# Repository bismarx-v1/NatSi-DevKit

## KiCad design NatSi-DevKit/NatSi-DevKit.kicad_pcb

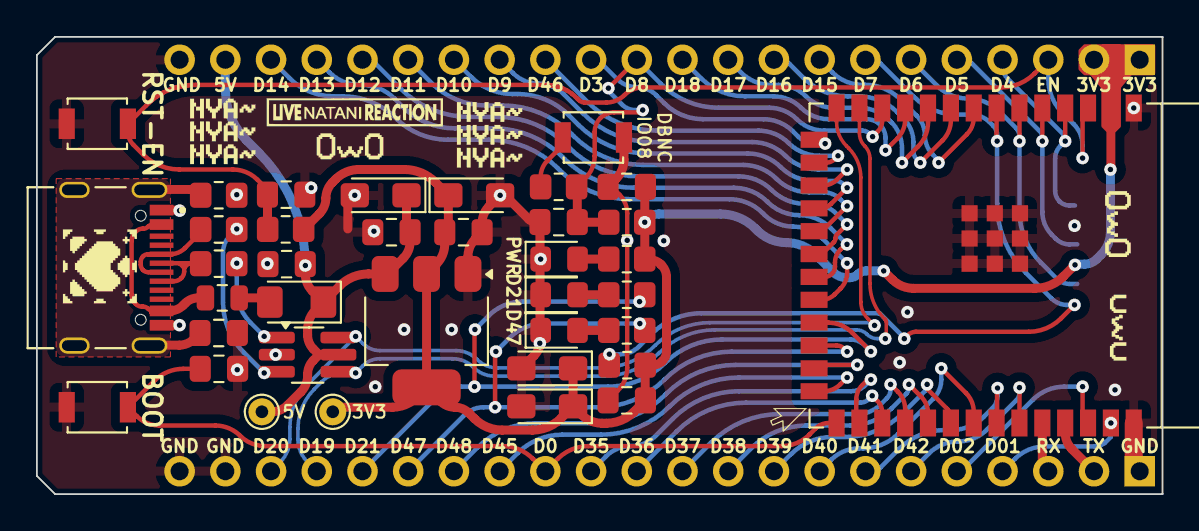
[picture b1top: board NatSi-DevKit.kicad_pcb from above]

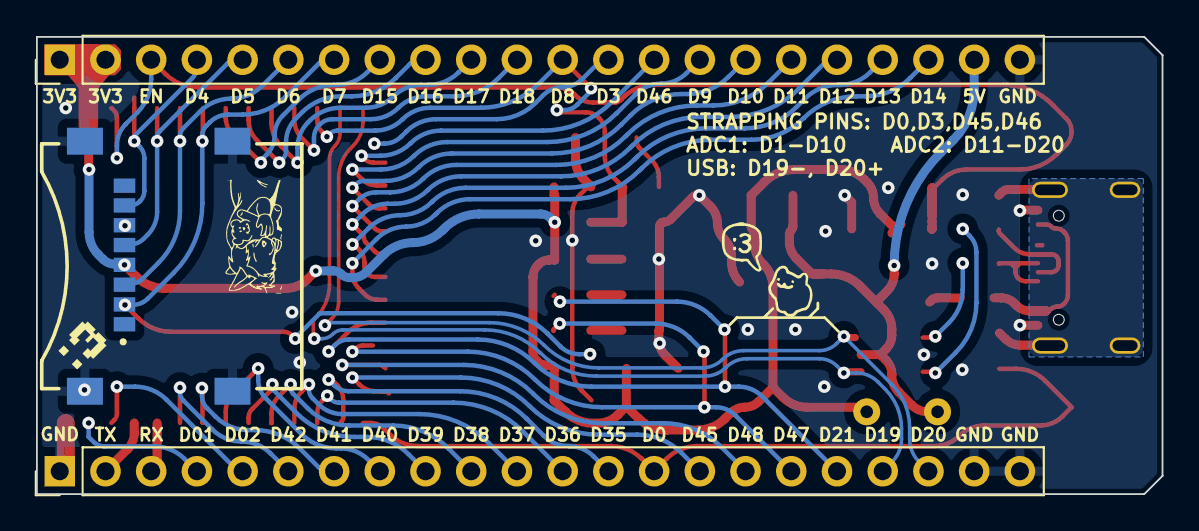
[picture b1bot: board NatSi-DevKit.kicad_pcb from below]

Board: 4 copper layers, 62.5 x 25.4 mm, 62 parts (12 on the bottom side), 51 nets.

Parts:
C1, C2, C3, C5, C6, C7, C9, C10, C13: 100nF; C_0805_2012Metric_Pad1.18x1.45mm_HandSolder
C4, C8, C11, C12: 10uF; CP_EIA-3216-18_Kemet-A_Pad1.58x1.35mm_HandSolder
D1: D_Schottky; D_1206_3216Metric_Pad1.42x1.75mm_HandSolder
D2, D3, D4: LED; LED_0805_2012Metric_Pad1.15x1.40mm_HandSolder
F1: Polyfuse; Fuse_0805_2012Metric
J1: USB_TypeC; HRO_TYPE-C-31-M-12
J2, J3: Conn_01x22_Pin; PinHeader_1x22_P2.54mm_Vertical
J4: MEM2067-02-180-00-A_REVB; MICRO_SD_CARD
R1: 100k; R_0805_2012Metric_Pad1.20x1.40mm_HandSolder
R2, R6, R7: 10k; R_0805_2012Metric_Pad1.20x1.40mm_HandSolder
R3, R4: 15R; R_0805_2012Metric_Pad1.20x1.40mm_HandSolder
R5: 1k; R_0805_2012Metric_Pad1.20x1.40mm_HandSolder
R8, R9, R10: 100R; R_0805_2012Metric_Pad1.20x1.40mm_HandSolder
SW1, SW2, SW3: SW_Push; SW_SPST_B3U-1000P
TP1, TP2: TestPoint; TestPoint_THTPad_D1.5mm_Drill0.7mm
TP3: TestPoint; NAT_PFP_IMG
TP4: TestPoint; BLAHAJ_IMG
TP5: TestPoint; BLAHAJ_SOLDER_LN_IMG
TP6: TestPoint; LIVE_NAT_REACTION_NEG
TP7, TP9#2: TestPoint; JOJO_SOLDER_IMG
TP8: TestPoint; FLO_SLEEP_IMG
TP9: TestPoint; CURSOR_IMG
TP10: TestPoint; COLON_3_CAT_IMG
TP11: TestPoint; COLON_3_IMG
TP12, TP14#2, TP14#3: TestPoint; COLON_3_SOLDER
TP13, TP15#2: TestPoint; OWO_IMG
TP14, TP16, TP16#2, TP16#3, TP16#4, TP16#5: TestPoint; NYA_IMG
TP15: TestPoint; UWU_IMG
U1: USBLC6-2SC6; TSOT-23-6_HandSoldering
U2: ESP32-S3-WROOM-1
U3: NCP1117-3.3_SOT223; SOT-223-3_TabPin2

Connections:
+3V3: C4.1, C5.1, C10.2, C11.1, C12.1, C13.1, J2.1, J2.2, J4.4 (VDD), R2.2, R6.2, R7.2, R8.1, TP1.1, U2.2 (3V3), U3.2 (VO)
+5V: C7.1, C8.1, C9.2, D1.1 (K), J2.21, TP2.1, U1.5, U3.3 (VI)
/BUTTON: R5.1, SW3.2
/SHLD: C1.2, J1.S1 (SHIELD), J1.S2 (SHIELD), J1.S3 (SHIELD), J1.S4 (SHIELD), R1.1
D+: J3.20, U1.6, U2.14 (IO20)
D+ IN: J1.A6 (DP1), J1.B6 (DP2), R3.1
D-: J3.19, U1.4, U2.13 (IO19)
D- IN: J1.A7 (DN1), J1.B7 (DN2), R4.1
EN: C2.1, J2.3, R2.1, SW1.2, U2.3 (EN)
GND: C1.1, C2.2, C3.2, C4.2, C5.2, C6.1, C7.2, C8.2, C9.1, C10.1, C11.2, C12.2, C13.2, D2.1 (K), D3.1 (K), D4.1 (K), J1.A1_B12 (GND), J1.B1_A12 (GND), J2.22, J3.1, J3.21, J3.22, J4.6 (VSS), J4.9 (SHIELD), J4.10 (SHIELD), J4.11 (SHIELD), J4.12 (SHIELD), R1.2, SW1.1, SW2.1, SW3.1, U1.2, U2.1 (GND), U2.40 (GND), U2.41 (GND), U3.1 (GND)
IO00_BOOT: C3.1, J3.14, SW2.2, U2.27 (IO0)
IO01: J3.4, U2.39 (IO1)
IO02: J3.5, U2.38 (IO2)
IO03: J2.13, U2.15 (IO3)
IO04_MISO: J2.4, J4.7 (DAT0), U2.4 (IO4)
IO05_CLK: J2.5, J4.5 (CLK), U2.5 (IO5)
IO06_MOSI: J2.6, J4.3 (CMD), U2.6 (IO6)
IO07_~CS: J2.7, J4.2 (CD/DAT3), R7.1, U2.7 (IO7)
IO8_BT: C6.2, J2.12, R5.2, R6.1, U2.12 (IO8)
IO09: J2.15, U2.17 (IO9)
IO10: J2.16, U2.18 (IO10)
IO11: J2.17, U2.19 (IO11)
IO12: J2.18, U2.20 (IO12)
IO13: J2.19, U2.21 (IO13)
IO14: J2.20, U2.22 (IO14)
IO15: J2.8, U2.8 (IO15)
IO16: J2.9, U2.9 (IO16)
IO17: J2.10, U2.10 (IO17)
IO18: J2.11, U2.11 (IO18)
IO21_LED: J3.18, R9.1, U2.23 (IO21)
IO35: J3.13, U2.28 (IO35)
IO36: J3.12, U2.29 (IO36)
IO37: J3.11, U2.30 (IO37)
IO38: J3.10, U2.31 (IO38)
IO39: J3.9, U2.32 (IO39)
IO40: J3.8, U2.33 (IO40)
IO41: J3.7, U2.34 (IO41)
IO42: J3.6, U2.35 (IO42)
IO45: J3.15, U2.26 (IO45)
IO46: J2.14, U2.16 (IO46)
IO47_LED: J3.17, R10.1, U2.24 (IO47)
IO48: J3.16, U2.25 (IO48)
unnamed: D1.2 (A), F1.1
unnamed: D2.2 (A), R8.2
unnamed: D3.2 (A), R9.2
unnamed: D4.2 (A), R10.2
unnamed: F1.2, J1.A4_B9 (VBUS), J1.B4_A9 (VBUS)
unnamed: R3.2, U1.1
unnamed: R4.2, U1.3
RXD0: J3.3, U2.36 (RXD0)
TXD0: J3.2, U2.37 (TXD0)

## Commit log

2024-10-07 Natani DevKit start-of
    PCB folder creation
2024-10-07 git ignore not working?
2024-10-08 some updates schematic
2024-10-08 update git ignore
2024-10-08 Schematic update
    Blocks, schematic finished
2024-10-09 PCB Layut update
2024-10-11 layout update
2024-10-13 pcb layout
2024-10-13 PCB routing update
    fuuyah a lot of pain to do these routes, Im also a shitty person.
2024-10-15 some 3d updates
2024-10-28 PCB update - traces
2024-10-29 Board update silkscreen and rouitign
2024-11-01 pcb update
2024-11-03 Booard update
2024-11-03 new silk, rounded tracks and soldermask
2024-11-04 PCB update silkscreen
2024-11-09 ooooh its done :3
2024-11-10 you will get your present soon cutie :3
2025-02-02 not sure whats the diff
2025-03-03 text update KiCAD 9.0 switch
2025-03-10 not sure
2025-06-01 some minor changes
2025-08-06 no updates
